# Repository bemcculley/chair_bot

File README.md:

chair_bot
=========

The end goal of this project is to be able to control a powered wheel chair using an Arduino and a Raspberry Pi (or other 'brain').
Specifically a Pride Jet 3 power chair with a Penny and Giles (P&G) PC200 joystick controller.

Packages needed:
(for wireless access point)
hostapd

(for xbox controller)
xboxdrv

reqs:
pip
hostapd
xboxdrv
python-pygame
python-serial

Thanks to Louis Thiery and Connor Wolf for their python / c SPI adaptor.

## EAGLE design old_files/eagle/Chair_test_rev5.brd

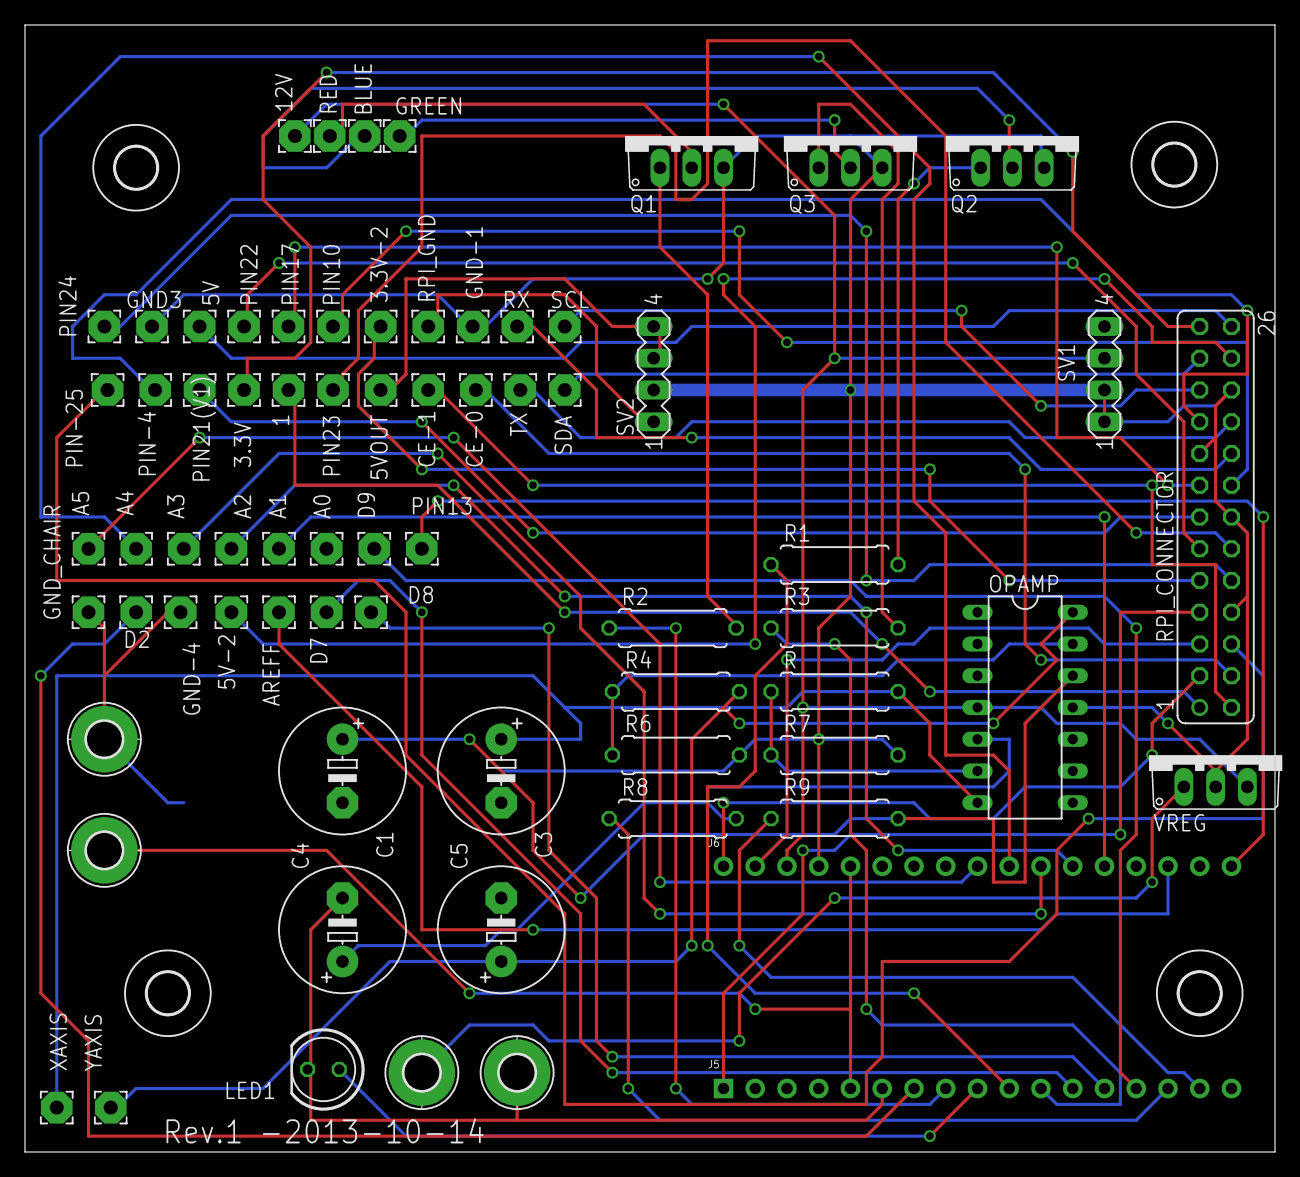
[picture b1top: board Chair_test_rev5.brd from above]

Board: 2 copper layers, 100.0 x 90.2 mm, 75 parts (0 on the bottom side), 57 nets.

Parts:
1, 3.3V, 3.3V-2, 5V-2, 5VOUT: 2,54/1,1
5V: 5v; 2,54/1,1
12V: 12v; 2,54/1,1
A0, A1, A2, A3, A4: 2,54/1,1
A5: a5; 2,54/1,1
AREFF: 2,54/1,1
BLUE: 2,54/1,1
C1, C3, C4, C5: 1uf; E5-10,5
CE-0, CE-1: 2,54/1,1
D2, D7, D8, D9: 2,54/1,1
GND, GND2: MOUNT-PAD-ROUND2.8; 2,8-PAD
GND3: gnd; 2,54/1,1
GND-1, GND-4: 2,54/1,1
GND_CHAIR: 2,54/1,1
GREEN: 2,54/1,1
H1, H2, H3, H5: MOUNT-HOLE3.3; 3,3
J5: HEAD17-NOSS
J6: HEAD17-NOSS-1
LED1: LED5MM
OPAMP: LM324N; DIL14
PIN10, PIN13, PIN17, PIN21(V1), PIN22, PIN23: 2,54/1,1
PIN24: pin24; 2,54/1,1
PIN-4, PIN-25: 2,54/1,1
Q1, Q2, Q3: tip120; TO220V
R, R4: 3.3k; 0309/10
R1, R2, R3, R6, R7: 2.2k; 0309/10
R8, R9: 10k; 0309/10
RED: 2,54/1,1
RPI_CONNECTOR: FE13-2
RPI_GND: 2,54/1,1
RST: MOUNT-PAD-ROUND2.8; 2,8-PAD
RX: 2,54/1,1
SCL: 2,54/1,1
SDA: 2,54/1,1
SV1, SV2: MA04-1
TX: 2,54/1,1
VCC: MOUNT-PAD-ROUND2.8; 2,8-PAD
VREG: 7812TV; TO220V
XAXIS: 2,54/1,1
YAXIS: 2,54/1,1

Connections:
5V: 5VOUT.1, SV2.3, SV2.4
5VGND: RPI_GND.1, SV2.1
A1: A1.1, J6.13
A2: A2.1, J6.12
A3: A3.1, J6.11
A4: A4.1, J6.10
A5: A5.1, J6.9
AREF: AREFF.1, J6.15
BLUE: J5.10, R1.1
D2/SDA: D2.1, J5.7
D4*: J5.9, LED1.A
D7: D7.1, J5.12
GND: C1.-, C3.-, C4.-, C5.-, GND.B2,8, GND2.B2,8, GND3.1, GND-1.1, GND-4.1, GND_CHAIR.1, J5.6, J6.4, LED1.K, OPAMP.11, Q1.3, Q2.3, Q3.3, R6.2, R7.2, RPI_CONNECTOR.8, RPI_CONNECTOR.14, RPI_CONNECTOR.17, RPI_CONNECTOR.22, SV1.1, SV1.2, SV2.2, VREG.2
GREEN: J5.11, R3.1
IO8: D8.1, J5.13
IO9*: D9.1, J5.14
IO13*: J6.17, PIN13.1
MISO: J6.2, RPI_CONNECTOR.5
MOSI: J5.1, RPI_CONNECTOR.7
unnamed: Q1.1, R2.2
unnamed: Q3.1, R3.2
unnamed: Q2.1, R1.2
unnamed: Q1.2, RED.1
unnamed: BLUE.1, Q2.2
unnamed: GREEN.1, Q3.2
unnamed: 3.3V-2.1, RPI_CONNECTOR.9
unnamed: C1.+, OPAMP.12, R9.2
unnamed: C3.+, OPAMP.7, R.2, XAXIS.1
unnamed: OPAMP.6, R.1, R7.1
unnamed: C5.+, OPAMP.14, R4.2, YAXIS.1
unnamed: OPAMP.13, R4.1, R6.1
unnamed: 1.1, RPI_CONNECTOR.1
unnamed: 3.3V.1, RPI_CONNECTOR.25
unnamed: RPI_CONNECTOR.23, SDA.1
unnamed: RPI_CONNECTOR.21, SCL.1
unnamed: PIN-4.1, RPI_CONNECTOR.19
unnamed: 5V-2.1, RPI_CONNECTOR.24
unnamed: RPI_CONNECTOR.20, TX.1
unnamed: RPI_CONNECTOR.18, RX.1
unnamed: PIN10.1, RPI_CONNECTOR.16
unnamed: PIN23.1, RPI_CONNECTOR.12
unnamed: PIN24.1, RPI_CONNECTOR.10
unnamed: PIN-25.1, RPI_CONNECTOR.6
unnamed: CE-0.1, RPI_CONNECTOR.4
unnamed: CE-1.1, RPI_CONNECTOR.2
NULL: 5V.1, RPI_CONNECTOR.26
PIN17: PIN17.1, RPI_CONNECTOR.15
PIN21: PIN21(V1).1, RPI_CONNECTOR.13
PIN22: PIN22.1, RPI_CONNECTOR.11
RED: J5.8, R2.1
RESET: J5.5, J6.5, RST.B2,8
SCK: J6.1, RPI_CONNECTOR.3
VCC: 12V.1, J6.3, OPAMP.4, SV1.3, VREG.3
VIN: VCC.B2,8, VREG.1
X: C4.+, OPAMP.5, R8.2
XAXIS: J5.15, R8.1
YAXIS: J5.16, R9.1

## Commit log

2013-10-04 Create arduino_api_control
2013-10-04 Rename arduino_api_control to arduino_spi_control
2013-10-04 Rename arduino_spi_control to arduino_spi_control.ino
2013-10-10 Initial commit of python spi code
2013-10-10 initial commit of python control script
2013-10-10 Initial commit of python chair control script
2013-10-10 testing some changes to deadzoning
2013-10-10 Update chair_controller.py
    Forgot the code from Garrett Owen was using the xbox_read module, d'oh
2013-10-11 trying deadzones with xboxdrv directly
2013-10-11 Update chair_controller.py
    fixing indent error
2013-10-14 Update to turn off LEDs
    Adding control to turn off LEDs
2013-10-14 change SPI bus to 4MHz
2013-10-15 python controller rewrite
2013-10-17 working test of new controller
2013-10-17 Adding stop command and fixing 'off' led option
2013-10-17 fixing x/y axis and some issues with incoming values not converting properly
2013-10-17 adding led dimming
2013-10-17 initial design for controller PCB
2013-10-18 changing spi bus to 1MHz and some debug output
2013-10-19 adding auto-stop and reverse control using a Parallax Ping sensor
2013-10-20 adding auto-stop and reverse with parallax Ping sensor, also fixes to python spi default clock speed
2014-01-26 loose files
2014-01-28 adding serial control
2014-01-28 adding arduino serial control test
2014-01-29 serial control
2014-01-30 use rx/tx pins instead of usb for serial comms
2014-01-30 adding servo 2
2015-03-27 finally saving some much needed modifications
2016-02-18 Adding ip script for finding the bot
2016-05-23 cleaning old files
2016-06-10 Breaking apart the chair control interfaces into a new class
2016-06-10 Bringing things back to working
2016-06-11 Making chair_serial pep8
2017-07-22 Adding everything from jazzy as of august 2016
2017-07-22 removing trash files
2017-07-23 adding serial range
2017-07-24 led top arduino code
2017-07-24 Updating chair serial runtime for new hat
2017-10-28 Adding new vegas style
